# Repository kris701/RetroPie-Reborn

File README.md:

# RetroPie-Reborn
This is a project to make a handheld console, that can run games from around PlayStation 1 and down.

Its basically a Raspberry Pi 4 that runs on RetroPie. It has small icons that show up in the corner, to give info in things such as how much battery is left or if the Pi is connected to Wifi.
Hardware wise, it has a 7' LCD screen, two small speakers, AUX output, USB-A output and USB-C charging port.
It has two 5000mAh batteries inside of it, giving it ~4 hours of normal usage before running out (but it really depends on what you use it for).
The console also has a little fan, that automatically turns on and off depending on the internal temperature of the Pi.

I originally designed it to include build in controllers on the side, however making the PCBs for the button pads didnt work out.
As a backup, i build in a connector on the two sides of the console, that can be used for future controller additions. 
Each side is basically mirrored, pinout wise, where each side supports up to 11 buttons (or 9 buttons and 2 analog inputs). Each side also have a GND and +5V pin.

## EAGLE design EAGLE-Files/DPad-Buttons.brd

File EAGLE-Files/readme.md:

# EAGLE Files

I made a bunch of custom PCB components for this project.
In this folder is all the EAGLE sketch and board files for it.
I milled all the boards on my CNC machine.

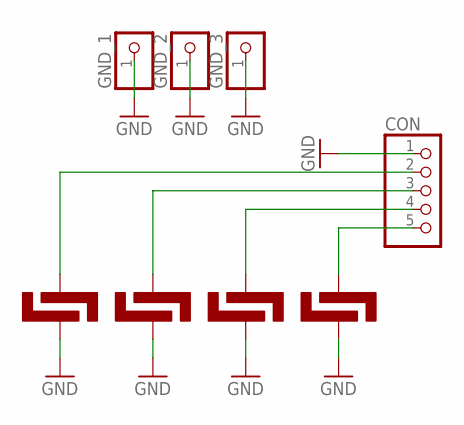
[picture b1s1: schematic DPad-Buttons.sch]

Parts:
BTN1, BTN2, BTN3, BTN4: BTN_5MM_LONG
CON: PINHD-1X5/90; 1X05/90
GND_1, GND_2, GND_3: PINHD-1X1; 1X01

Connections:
GND: BTN1.P$2, BTN2.P$2, BTN3.P$2, BTN4.P$2, CON.1, GND_1.1, GND_2.1, GND_3.1
unnamed: BTN1.P$1, CON.2
unnamed: BTN4.P$1, CON.5
unnamed: BTN3.P$1, CON.4
unnamed: BTN2.P$1, CON.3

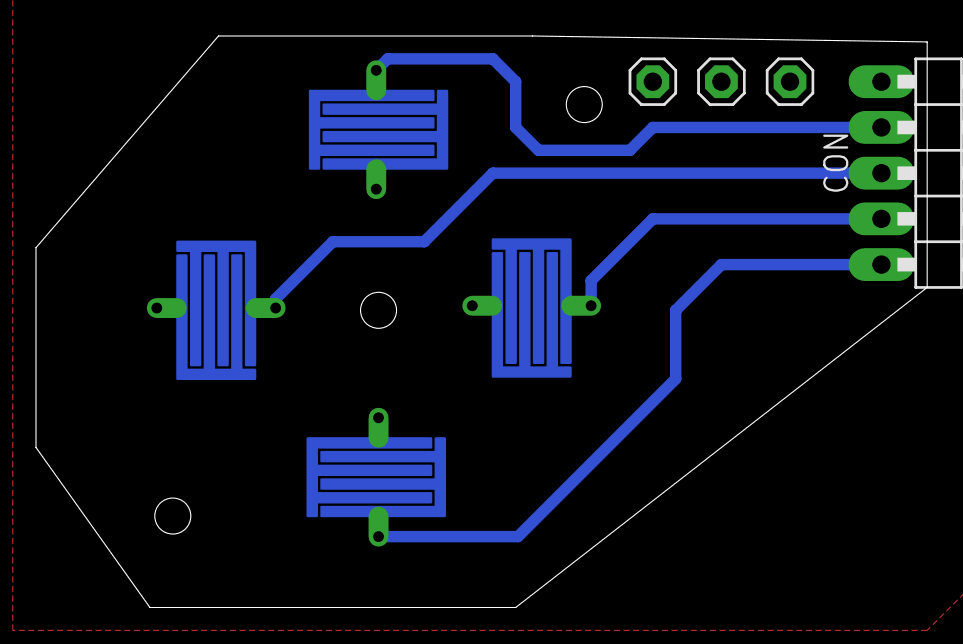
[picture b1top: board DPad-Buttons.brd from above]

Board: 2 copper layers, 49.5 x 31.8 mm, 8 parts (0 on the bottom side), 5 nets.

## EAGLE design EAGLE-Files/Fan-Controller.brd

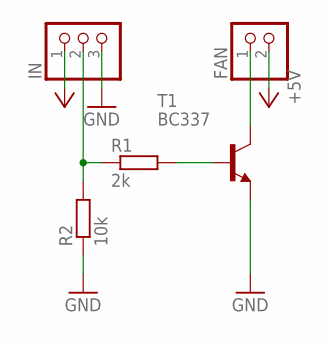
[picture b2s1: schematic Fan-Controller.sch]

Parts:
FAN: PINHD-1X2/90; 1X02/90
IN: PINHD-1X3/90; 1X03/90
R1: 2k; 0204/7
R2: 10k; 0204/7
T1: BC337; TO92

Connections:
+5V: FAN.2, IN.1
GND: IN.3, R2.1, T1.1 (E)
unnamed: FAN.1, T1.3 (C)
unnamed: R1.2, T1.2 (B)
unnamed: IN.2, R1.1, R2.2

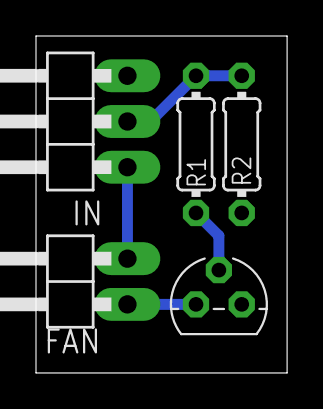
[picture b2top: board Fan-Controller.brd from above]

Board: 2 copper layers, 13.9 x 18.7 mm, 5 parts (0 on the bottom side), 5 nets.

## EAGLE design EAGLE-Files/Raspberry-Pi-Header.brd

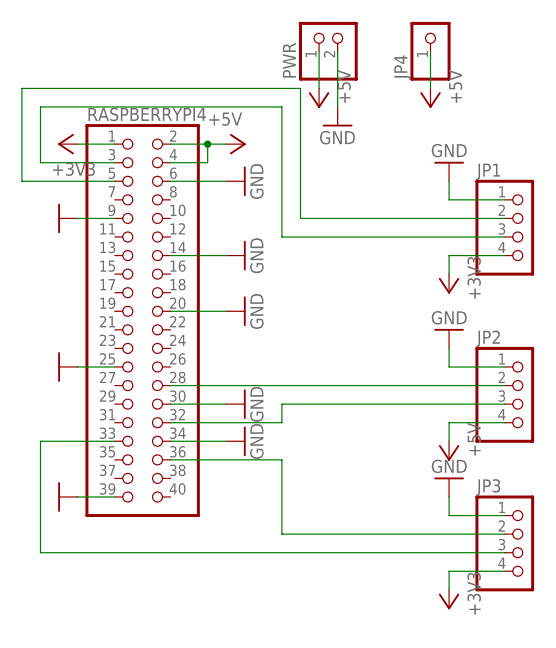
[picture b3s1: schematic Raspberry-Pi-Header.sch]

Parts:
JP1, JP2, JP3: PINHD-1X4/90; 1X04/90
JP4: PINHD-1X1; 1X01
PWR: PINHD-1X2/90; 1X02/90
RASPBERRYPI4: PINHD-2X20; 2X20

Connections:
+3V3: JP1.4, JP3.4, RASPBERRYPI4.1
+5V: JP2.4, JP4.1, PWR.1, RASPBERRYPI4.2, RASPBERRYPI4.4
GND: JP1.1, JP2.1, JP3.1, PWR.2, RASPBERRYPI4.6, RASPBERRYPI4.9, RASPBERRYPI4.14, RASPBERRYPI4.20, RASPBERRYPI4.25, RASPBERRYPI4.30, RASPBERRYPI4.34, RASPBERRYPI4.39
GPIO1: JP2.2, RASPBERRYPI4.28
GPIO12: JP2.3, RASPBERRYPI4.32
GPIO13: JP3.3, RASPBERRYPI4.33
GPIO16: JP3.2, RASPBERRYPI4.36
SCL: JP1.2, RASPBERRYPI4.5
SDA: JP1.3, RASPBERRYPI4.3

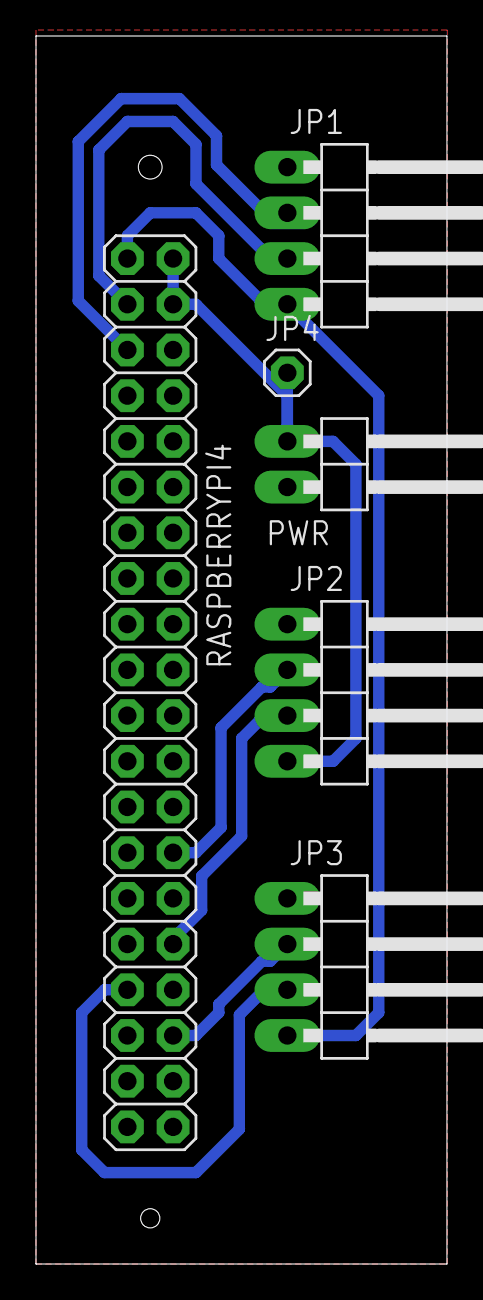
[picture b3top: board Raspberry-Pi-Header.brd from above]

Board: 2 copper layers, 22.8 x 68.2 mm, 6 parts (0 on the bottom side), 9 nets.

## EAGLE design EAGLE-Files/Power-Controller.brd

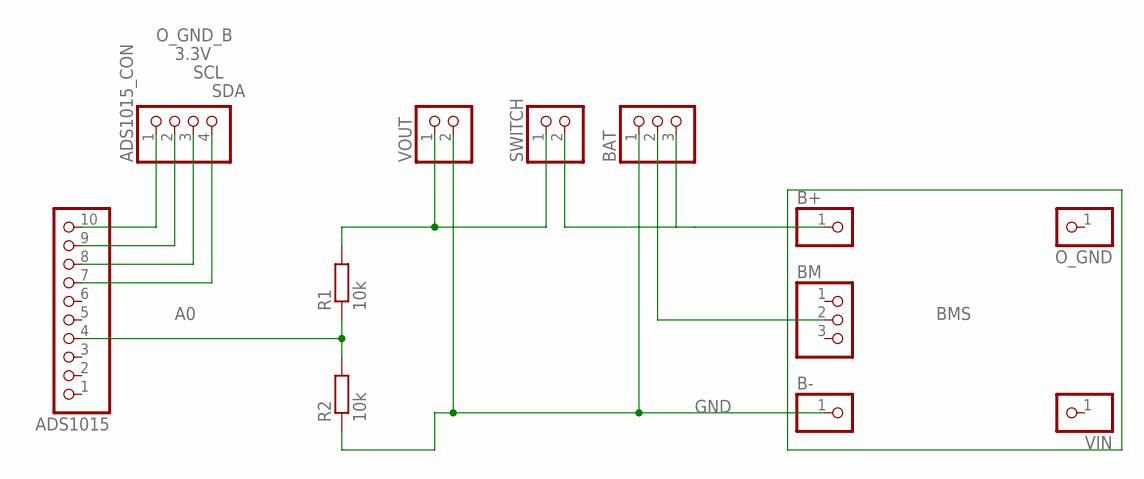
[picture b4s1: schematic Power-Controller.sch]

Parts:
ADS1015: PINHD-1X10; 1X10
ADS1015_CON: PINHD-1X4/90; 1X04/90
B+: PINHD-1X1; 1X01
B-: PINHD-1X1; 1X01
BAT: PINHD-1X3/90; 1X03/90
BM: PINHD-1X3; 1X03
O_GND: PINHD-1X1; 1X01
R1, R2: 10k; 0204/7
SWITCH: PINHD-1X2; 1X02
VIN: PINHD-1X1; 1X01
VOUT: PINHD-1X2/90; 1X02/90

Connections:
3.3V: ADS1015.9, ADS1015_CON.2
A0: ADS1015.4, R1.1, R2.2
GND: B-.1, BAT.1, R2.1, VOUT.2
unnamed: B+.1, BAT.3, SWITCH.2
unnamed: BAT.2, BM.2
unnamed: R1.2, SWITCH.1, VOUT.1
O_GND_B: ADS1015.10, ADS1015_CON.1
SCL: ADS1015.8, ADS1015_CON.3
SDA: ADS1015.7, ADS1015_CON.4

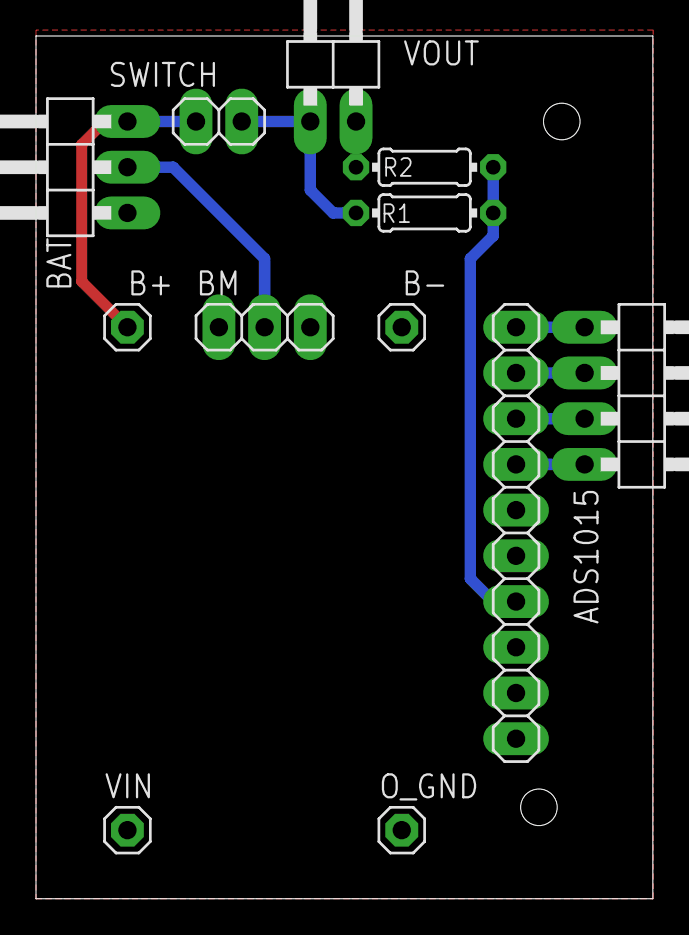
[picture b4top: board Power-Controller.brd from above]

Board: 2 copper layers, 34.3 x 47.9 mm, 12 parts (0 on the bottom side), 9 nets.

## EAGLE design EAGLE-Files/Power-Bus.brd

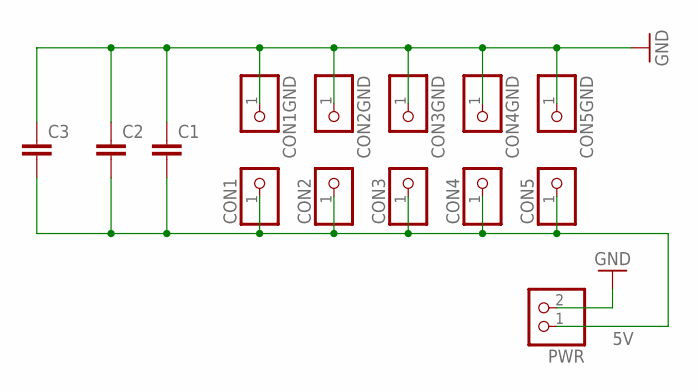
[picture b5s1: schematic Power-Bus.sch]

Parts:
C1, C2, C3: C-EU050-025X075; C050-025X075
CON1, CON1GND, CON2, CON2GND, CON3, CON3GND, CON4, CON4GND, CON5, CON5GND: PINHD-1X1; 1X01
PWR: PINHD-1X2/90; 1X02/90

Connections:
5V: C1.2, C2.2, C3.2, CON1.1, CON2.1, CON3.1, CON4.1, CON5.1, PWR.1
GND: C1.1, C2.1, C3.1, CON1GND.1, CON2GND.1, CON3GND.1, CON4GND.1, CON5GND.1, PWR.2

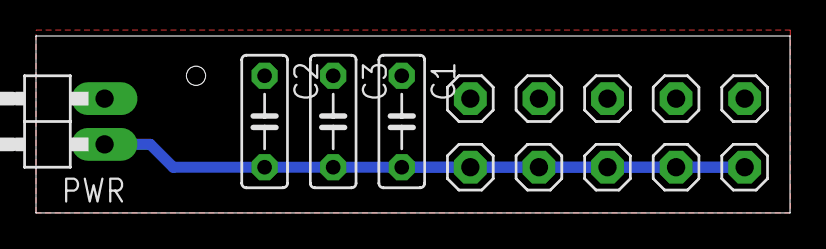
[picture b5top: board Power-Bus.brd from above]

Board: 2 copper layers, 41.9 x 9.8 mm, 14 parts (0 on the bottom side), 2 nets.

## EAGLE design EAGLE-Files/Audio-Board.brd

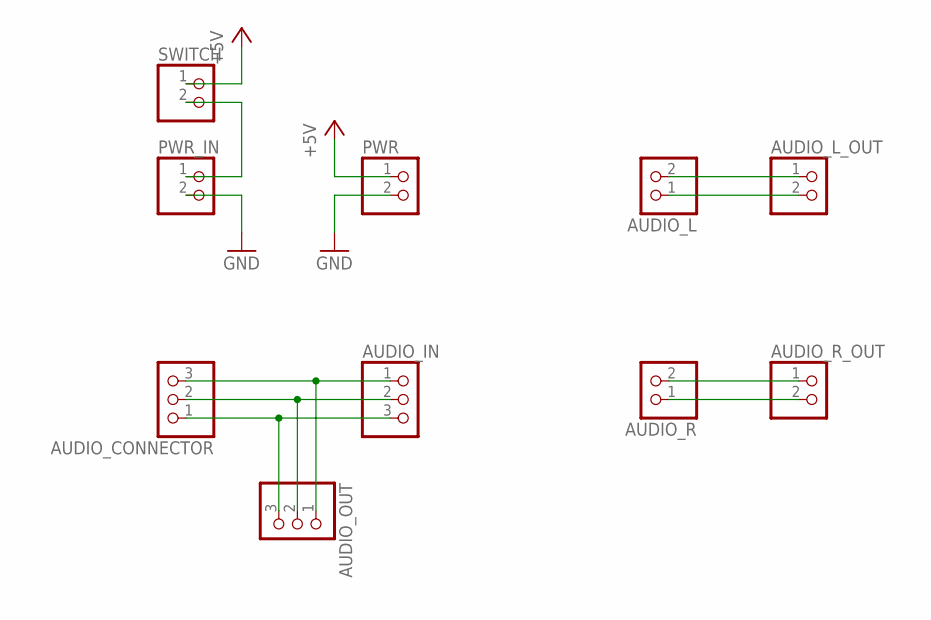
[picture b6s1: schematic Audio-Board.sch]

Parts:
AUDIO_CONNECTOR: PINHD-1X3; 1X03
AUDIO_IN: PINHD-1X3; 1X03
AUDIO_L: PINHD-1X2; 1X02
AUDIO_L_OUT: PINHD-1X2/90; 1X02/90
AUDIO_OUT: PINHD-1X3; 1X03
AUDIO_R: PINHD-1X2; 1X02
AUDIO_R_OUT: PINHD-1X2/90; 1X02/90
PWR: PINHD-1X2; 1X02
PWR_IN: PINHD-1X2/90; 1X02/90
SWITCH: PINHD-1X2/90; 1X02/90

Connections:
+5V: PWR.1, SWITCH.1
GND: PWR.2, PWR_IN.2
unnamed: AUDIO_CONNECTOR.3, AUDIO_IN.1, AUDIO_OUT.1
unnamed: AUDIO_CONNECTOR.2, AUDIO_IN.2, AUDIO_OUT.2
unnamed: AUDIO_CONNECTOR.1, AUDIO_IN.3, AUDIO_OUT.3
unnamed: AUDIO_L.1, AUDIO_L_OUT.2
unnamed: AUDIO_L.2, AUDIO_L_OUT.1
unnamed: AUDIO_R.2, AUDIO_R_OUT.1
unnamed: AUDIO_R.1, AUDIO_R_OUT.2
unnamed: PWR_IN.1, SWITCH.2

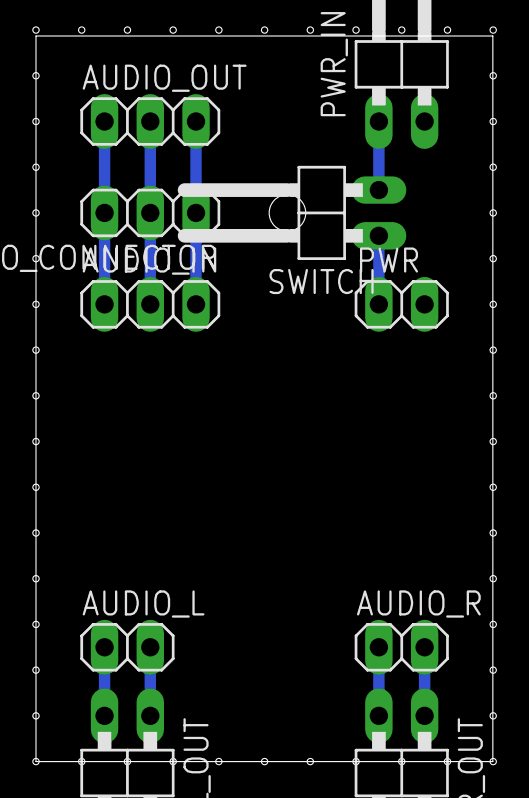
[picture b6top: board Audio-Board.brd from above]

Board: 2 copper layers, 25.4 x 40.3 mm, 10 parts (0 on the bottom side), 10 nets.

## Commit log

2023-08-28 Add .gitattributes, .gitignore, and README.md.
2023-08-28 Add project files.
2023-08-28 Added config info
2023-08-28 * Added initial pyton code * Added readmes
2023-08-28 Added initial EAGLE files
2023-08-28 Added a parts list
2023-08-28 Added initial icons
2023-08-29 * Updated gitignore * Updated some of the EAGLE boards
2023-08-29 Removed unneeded file
2023-08-29 * Updated gitignore * Updated some boards and schematics
2023-08-29 Fixed a board
2023-08-30 Added a custom boot screen file
2023-09-01 * Updated the header board * Added a audio board * Added a power controller board * Updated gitignore
2023-09-03 * Fixed a small error in the Raspberry Pi GPIO Header board (pins was offset) * Added the initial 3d print files
2023-09-07 Updated the 3D Print files * The inner bracket is finished * The outer shell is updated (WIP)
2023-09-07 Moved some files
2023-09-07 Refactoring and structuring
2023-09-07 Refactoring
2023-09-07 Added preliminary bluetooth runner code
2023-09-07 Initial implementation of the performance icon runner
2023-09-07 Initial implementation of the battery icon runner
2023-09-08 * Indexed all the battery icons * Added a Fan Icon Runner to control the fan * Updated icons
2023-09-08 Split some runners up in two and updated icons
2023-09-08 Fixed a reference error
2023-09-08 Updated icon runners
2023-09-12 Updated the 3d models
2023-09-17 Updated design files
2023-09-17 Converted the setup file to a markdown format
2023-09-23 Updated board layout
2023-09-24 Updated boards and 3d models
2023-09-25 Updated board layouts
2023-10-03 Updated boards and models
2023-11-12 Updated the teensy code to fully work with the controller
2023-11-12 Shorter bootscreen
2023-11-12 Fixes
2023-11-12 Bug fix
2023-11-12 Fix part 1
2023-11-12 Fix part 2
2023-11-12 Key fix
2023-11-12 Map fix
2023-11-12 Test
2023-11-12 Fixed bad timer
2023-11-12 debug
2023-11-12 Path updatez
2023-11-12 String fix
2023-11-12 Correct offset
2023-11-12 Offset fix
2023-11-12 Removes debug info
2023-11-12 New implementation of the ADC
2023-11-12 Reference fix
2023-11-12 More "reasonable" charge voltage values
2023-11-12 Wait update
2023-11-12 check
2023-11-12 Fix pop
2023-11-12 Initial pwm setup
2023-11-12 WIP on the other components
2023-11-13 Fixed pin
2023-11-13 Dict fix
2023-11-13 Removed debug stuff
2023-11-13 New fan icons
2023-11-13 Only updates if neededd
2023-11-13 Bugfix and updated project file
2023-11-14 average battery level
2023-11-14 Reduced the battery map
2023-11-14 Reduced refresh rate
2023-11-14 Updated fan speeds
2023-11-14 Updated bootscreen
2023-11-14 Rooted icon paths
2023-11-14 Fixed paths
2023-11-14 Updated some items
2023-11-14 Updated some icons
2023-11-14 Bluetooth Icon update
2023-11-14 Updated fan levels
2023-11-14 Puts some more items in a try catch (since they can fail)
2023-11-14 Updated icons and caps
2023-11-14 Adds timeout for processes
2023-11-14 Fixed direction
2023-11-15 Calibrated battery meter
2023-12-16 Updated models
2023-12-17 Tweaked the battery icon runner
2023-12-18 Small icon fix
2023-12-18 Removed a bunch of old files
2023-12-18 Added readmes
2023-12-18 Battery tweaks
2023-12-18 fixing issues in PNGView
2023-12-18 null test
2023-12-18 null check
2023-12-18 Removed bad import
2023-12-18 debug check
2023-12-18 debug fix
2023-12-18 debug test
2023-12-18 Removed debug text
2023-12-19 Transparent fix
2023-12-19 Added a new runner
2023-12-19 Download fix
2023-12-19 Average fix
2023-12-19 Calibrated battery
2023-12-19 Uses average CPU temp instead of directly the current one
2023-12-19 Set the fan to turn on at higher temps
2023-12-19 Added a time runner
2023-12-19 Enables the runner
2023-12-19 Icon offset fix
2023-12-19 Margin fix
2023-12-30 Added stand iges
2024-08-03 Updated all boards for JLCPCB order
    Also added the controller boards and schematics back
2024-08-24 Updated the DPad and Four Buttons PCB designs for production
